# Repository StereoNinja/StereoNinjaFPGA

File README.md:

# StereoNinjaFPGA
Experimental FPGA project for streaming two MIPI CSI camera IMX219 streams to an HDMI monitor using a ULX3S FPGA board

Todos

- [x] HDMI Stream 640x480 60FPS
- [x] HDMI Stream 800x600 60 FPS
- [x] HDMI Stream 1280x720 60 FPS
- [ ] HDMI Stream 1920x1080 60FP -not possible
- [x] Initialisation Videostream IMX219 at 916Mbit/s per Lane 
- [x] MIPI SoT Decoding
- [x] MIPI Syncbyte Decoding
- [x] MIPI Header Decoding
- [x] MIPI Protocoll Decoding
- [x] Writing MIPI Videostream in Dualport Ram
- [x] Passthrough IMX219 to HDMI at 640x480 Pixel in greyscale
- [x] Debayering for Colors -works partially 
- [ ] Testing IMX219 at other Resolutions 
- [ ] Testing Design with two Cameras
- [ ] Creating Side-by-Side(Half) HDMI 3D Output at 1280x720 

- /DOCS_ULX3S Some Documentations for used Hardware and Protocoll Spezifications
- /ULX3S_ninja PCB for Adapterboard
- /old Some old Projects for Testing
- /src Source Code for StereoninjaFPGA

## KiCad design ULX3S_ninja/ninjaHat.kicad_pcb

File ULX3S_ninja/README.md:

# ULX3S Ninja

PCB for connecting 2 Raspi cams to an ULX3S FPGA board.
The cameras are connected using a DVI cable and the StereoNinja camera board, see https://github.com/StereoNinja/StereoNinja

# Pinout ULX3S

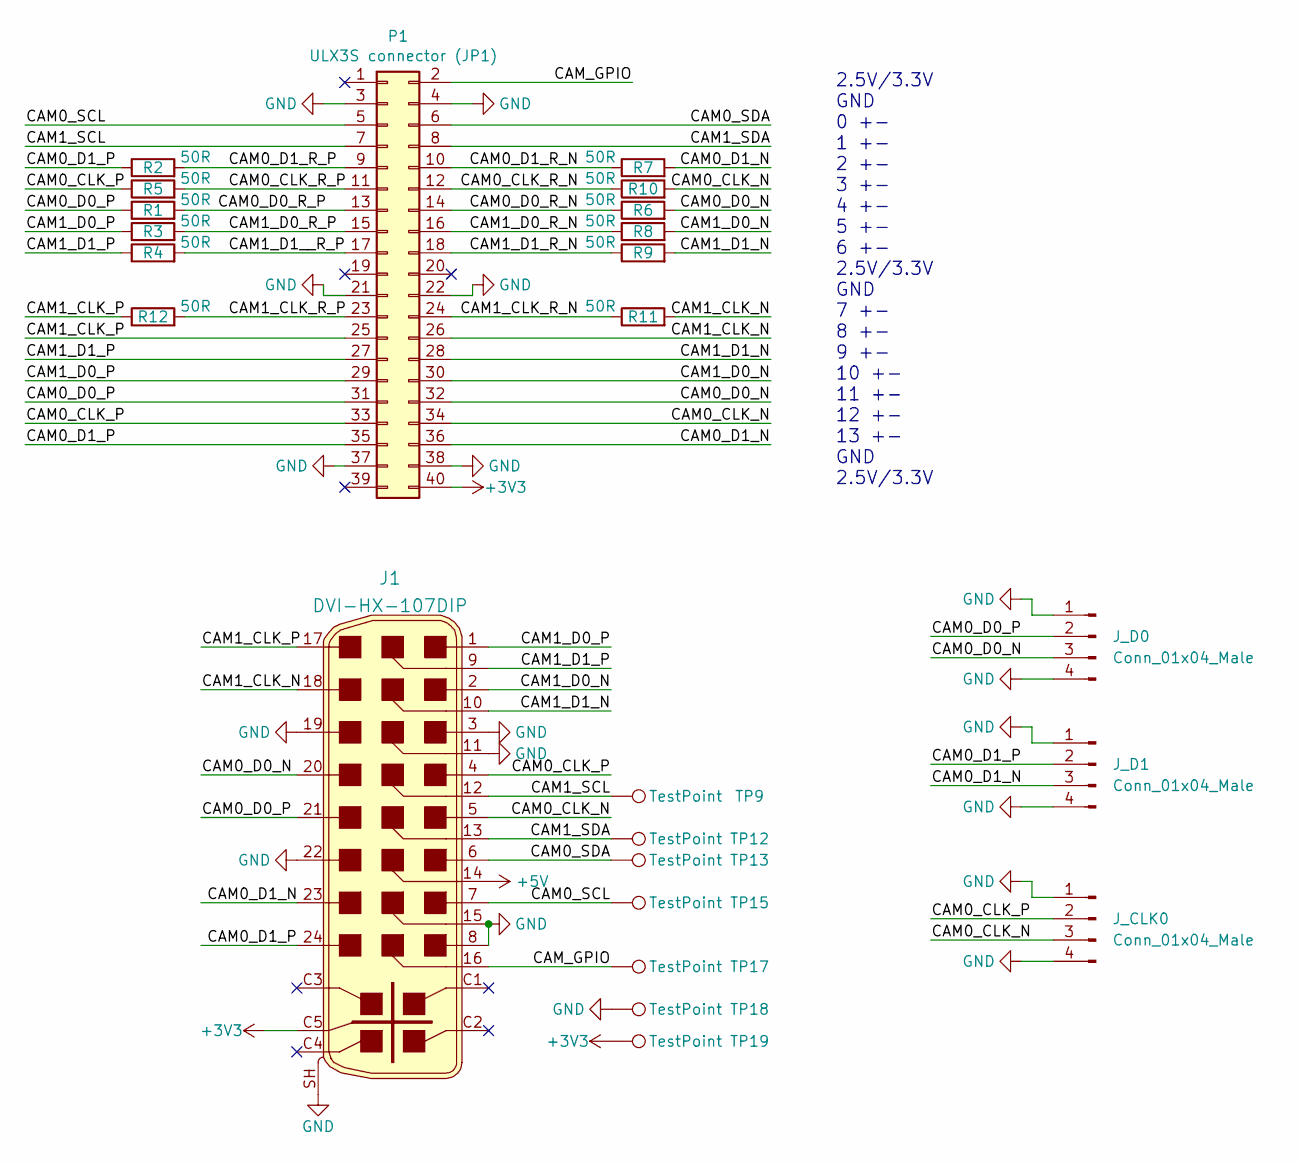
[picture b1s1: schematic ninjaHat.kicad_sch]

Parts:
J1: DVI-HX-107DIP; DVI_Female_74320-9010; MPN DVI-HX-107DIP; LCSC# C2936242
J_CLK0: Conn_01x04_Male; PinHeader_1x04_P2.54mm_Vertical
J_D0, J_D1: Conn_01x04_Male; PinHeader_1x04_P2.54mm_Vertical
P1: ULX3S connector (JP1); PinSocket_2x20_P2.54mm_Vertical
R1, R2, R3, R4, R5, R6, R7, R8, R9, R10, R11, R12: 50R; R_0805_2012Metric
TP9, TP12, TP13, TP15, TP17, TP18, TP19: TestPoint; TestPoint_Pad_D1.5mm

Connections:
+3V3: J1.C5, P1.40, TP19.1
+5V: J1.14
/CAM0_CLK_N: J1.5, J_CLK0.3, P1.34, R10.2
/CAM0_CLK_P: J1.4, J_CLK0.2, P1.33, R5.1
/CAM0_CLK_R_N: P1.12, R10.1
/CAM0_CLK_R_P: P1.11, R5.2
/CAM0_D0_N: J1.20, J_D0.3, P1.32, R6.2
/CAM0_D0_P: J1.21, J_D0.2, P1.31, R1.1
/CAM0_D0_R_N: P1.14, R6.1
/CAM0_D0_R_P: P1.13, R1.2
/CAM0_D1_N: J1.23, J_D1.3, P1.36, R7.2
/CAM0_D1_P: J1.24, J_D1.2, P1.35, R2.1
/CAM0_D1_R_N: P1.10, R7.1
/CAM0_D1_R_P: P1.9, R2.2
/CAM0_SCL: J1.7, P1.5, TP15.1
/CAM0_SDA: J1.6, P1.6, TP13.1
/CAM1_CLK_N: J1.18, P1.26, R11.2
/CAM1_CLK_P: J1.17, P1.25, R12.1
/CAM1_CLK_R_N: P1.24, R11.1
/CAM1_CLK_R_P: P1.23, R12.2
/CAM1_D0_N: J1.2, P1.30, R8.2
/CAM1_D0_P: J1.1, P1.29, R3.1
/CAM1_D0_R_N: P1.16, R8.1
/CAM1_D0_R_P: P1.15, R3.2
/CAM1_D1_N: J1.10, P1.28, R9.2
/CAM1_D1_P: J1.9, P1.27, R4.1
/CAM1_D1_R_N: P1.18, R9.1
/CAM1_D1__R_P: P1.17, R4.2
/CAM1_SCL: J1.12, P1.7, TP9.1
/CAM1_SDA: J1.13, P1.8, TP12.1
/CAM_GPIO: J1.16, P1.2, TP17.1
GND: J1.3, J1.8, J1.11, J1.15, J1.19, J1.22, J1.SH, J_CLK0.1, J_CLK0.4, J_D0.1, J_D0.4, J_D1.1, J_D1.4, P1.3, P1.4, P1.21, P1.22, P1.37, P1.38, TP18.1

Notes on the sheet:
2.5V/3.3V GND 0 +- 1 +- 2 +- 3 +- 4 +- 5 +- 6 +- 2.5V/3.3V GND 7 +- 8 +- 9 +- 10 +- 11 +- 12 +- 13 +- GND 2.5V/3.3V

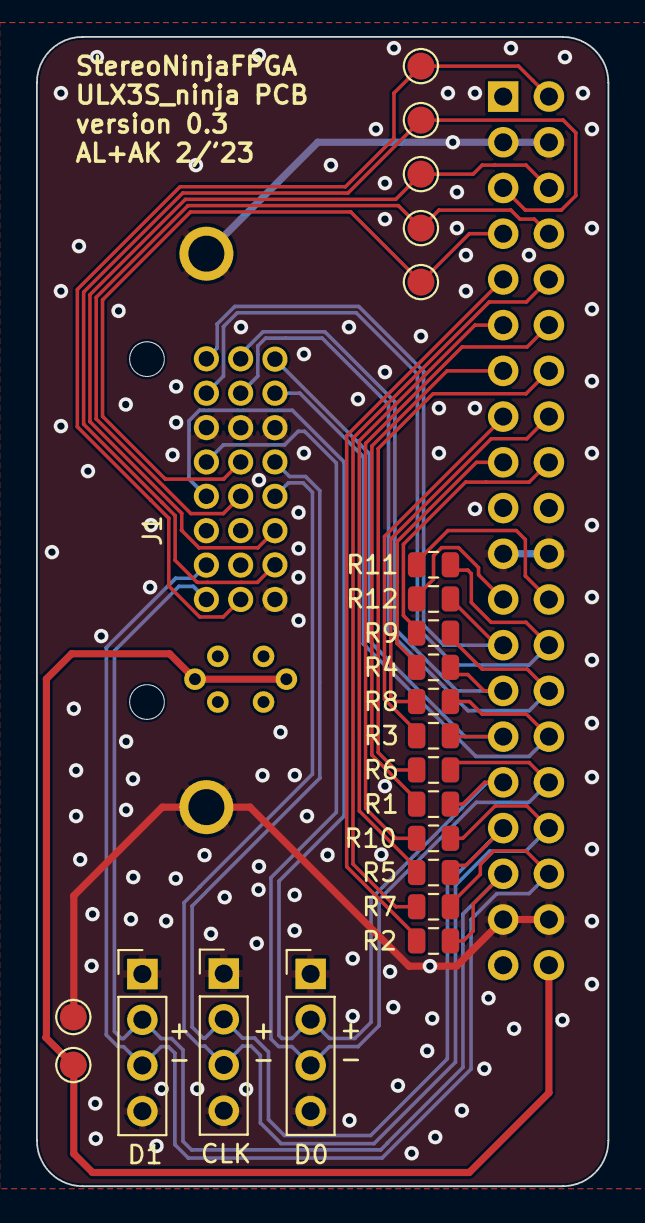
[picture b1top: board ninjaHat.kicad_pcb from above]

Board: 2 copper layers, 31.8 x 63.8 mm, 24 parts (1 on the bottom side), 31 nets.

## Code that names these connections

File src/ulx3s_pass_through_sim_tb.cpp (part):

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		//tb->m_core->lane0=((lane0reg)&(1<<i))/(pow(2,i));
		//tb->m_core->lane1=((lane1reg)&(1<<i))/(pow(2,i));
		if(i==0){
			tb->m_core->cam0_d0_r_p=1;
			tb->m_core->cam0_d0_r_n=1;
			tb->m_core->cam0_d1_r_p=1;
			tb->m_core->cam0_d1_r_n=1;
		}
		if(i==10){
			tb->m_core->cam0_d0_r_p=0;
			tb->m_core->cam0_d0_r_n=1;
			tb->m_core->cam0_d1_r_p=0;
			tb->m_core->cam0_d1_r_n=1;
		}
		if(i==20)
		{
			tb->m_core->cam0_d0_r_p=0;
			tb->m_core->cam0_d0_r_n=0;
			tb->m_core->cam0_d1_r_p=0;
			tb->m_core->cam0_d1_r_n=0;
		}
		if(i>=200)
		{
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
		}
		if(i==5000){
			tb->m_core->cam0_d0_r_p=1;
			tb->m_core->cam0_d0_r_n=1;
			tb->m_core->cam0_d1_r_p=1;
			tb->m_core->cam0_d1_r_n=1;
		}
		if(i==5010){
			tb->m_core->cam0_d0_r_p=0;
			tb->m_core->cam0_d0_r_n=1;
			tb->m_core->cam0_d1_r_p=0;
			tb->m_core->cam0_d1_r_n=1;
		}
		if(i==5080)
		{
			tb->m_core->cam0_d0_r_p=0;
			tb->m_core->cam0_d0_r_n=0;
			tb->m_core->cam0_d1_r_p=0;
			tb->m_core->cam0_d1_r_n=0;
		}
		if(i>=5250)
		{
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
		}
		if(i==10000){
			tb->m_core->cam0_d0_r_p=1;
			tb->m_core->cam0_d0_r_n=1;
			tb->m_core->cam0_d1_r_p=1;
			tb->m_core->cam0_d1_r_n=1;
		}
		if(i==10010){
			tb->m_core->cam0_d0_r_p=0;
			tb->m_core->cam0_d0_r_n=1;
			tb->m_core->cam0_d1_r_p=0;
			tb->m_core->cam0_d1_r_n=1;
		}
		if(i==10080)
		{
			tb->m_core->cam0_d0_r_p=0;
			tb->m_core->cam0_d0_r_n=0;
			tb->m_core->cam0_d1_r_p=0;
			tb->m_core->cam0_d1_r_n=0;
		}
		if(i>=10250)
		{
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		}

		if(i==15000){
			tb->m_core->cam0_d0_r_p=1;
			tb->m_core->cam0_d0_r_n=1;
			tb->m_core->cam0_d1_r_p=1;
			tb->m_core->cam0_d1_r_n=1;
		}
		if(i==15010){
			tb->m_core->cam0_d0_r_p=0;
			tb->m_core->cam0_d0_r_n=1;
			tb->m_core->cam0_d1_r_p=0;
			tb->m_core->cam0_d1_r_n=1;
		}
		if(i==15080)
		{
			tb->m_core->cam0_d0_r_p=0;
			tb->m_core->cam0_d0_r_n=0;
			tb->m_core->cam0_d1_r_p=0;
			tb->m_core->cam0_d1_r_n=0;
		}
		if(i>=15250)
		{
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
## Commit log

2022-07-19 added initial pcb info
2022-07-19 fix markdown
2022-07-19 typo
2022-07-19 added more links
2022-08-04 added pcb
2022-08-04 Changed some tracks' width to 0,2mm
    was 0,152mm before. Also took a overview over PCB. looks good so far
2022-09-01 Toolchain Description
2022-09-16 TestProjects added
2022-09-16 ULX3S_HDMI_test working
2022-10-20 Primitives
2022-10-25 Simulation HDMI_test working
    No Simulation of primitive EHXPLLL possible. 250MHz clock generated by testbench.
2022-10-26 Testbench with image output
    This reverts commit 0d69ef920c5397d0e41a426d8489994116fe7cb2.
2022-10-27 image.ppm
2022-10-29 Component TMDS_Encoder
2022-10-29 Makefile for Creating Projects
2022-10-30 HDMI Transciever working
2022-11-02 HDMI_Transciever_Test working
    changed TMDS Encoder,TMDS_Transciever
2022-11-03 SDRAM DOC
2022-11-03 HDMI Transciever Test Image
2022-11-03 800x600p working
    DDR2 outputs working 800x600p 40Mhz pixclk 200Mhz TMDS_clk
2022-11-03 800x600p Image
2022-11-06 Serial Connection working
    Serial Connection USB1 video enable
2022-11-10 working on Ram_Controller
2022-11-13 Ram Controller working
2022-11-16 Ram controller working without pixel errors
    changes made in Ram_Controller.v to increase read speed
2022-11-19 canges
2022-11-21 camera doc added
2022-12-02 I2C working
2022-12-06 Camera Init working
2022-12-11 now changing mipi to 2:1 ddrinput
    cam0clk is ddrclock bitclk!! not byteclk
2022-12-13 new Revision for FPGA Ninja
    Termination Resistors and 4 Impus per lane and clk
2022-12-13 Changed circuit
2022-12-13 small aesthetic change sin schematic; added schematic png
2022-12-13 updated text; added pinout png
2022-12-13 fixed link to png
2023-01-08 PCB work and pin mapping changed
    Did a first PCB layout
    changed the pin mapping towards FPGAs four easier routing, schematic need to be rechecked!
2023-01-15 Pin Mapping changed again
    Please check
2023-01-19 Layout finished
2023-01-19 Schematic fix
2023-01-23 added pinheaders for D0 D1 and CLK (cam0 only) for debugging
2023-01-23 added 2nd gnd pin to debugging connectors
2023-02-01 fixed pin header footprint
2023-02-08 Recieving of Sync Byte
2023-02-09 Detection of SOT an Sync Byte definatly working
2023-02-12 Decoding of Header is working
2023-02-14 re_detect signal working
2023-02-15 WOrking header Decoding
2023-02-15 some thinks work some not
2023-02-16 Bug fixed
2023-02-16 Bug fixed stabel Recieving data!
2023-02-19 test
2023-02-20 Camera working but pixelfehler
2023-02-20 working on crc
2023-02-21 CRC Code calculation correct
2023-03-01 changed constraint to 500MHz
2023-03-14 Serial Ram Debug
2023-03-15 Serial debugger
2023-03-15 debugger working
2023-03-26 350Mhz
2023-03-27 changes iddrx1f
2023-04-11 new orga
2023-04-11 readme
2023-04-11 image
2023-04-11 simualtion Topmodule
2023-04-19 pseudo debayering
2023-04-27 better logo
2023-05-04 Bachelor Thesis
2023-05-09 hs only
2023-05-09 debayer
2023-05-09 working hs only mode
2023-05-14 problem hsync hdmi debayer
2023-05-15 debayer on testpattern working
